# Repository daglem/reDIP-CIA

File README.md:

# reDIP CIA

## MOS 6520 PIA / MOS 6522 VIA / MOS 6526/8520/8521 CIA FPGA replacement

## Overview
The reDIP CIA is an open source FPGA board which combines the following in a
DIP-40 size package:

* Lattice iCE5LP1K FPGA
* 1Mbit FLASH
* 5V tolerant I/O

The reDIP CIA provides an open source hardware platform for MOS 6520 PIA /
MOS 6522 VIA / MOS 6526/8520/8521 CIA replacements.

Designs for the iCE5LP1K FPGA can be processed by
[yosys](https://github.com/YosysHQ/yosys/) and
[nextpnr](https://github.com/YosysHQ/nextpnr/).

## I/O interfaces

### DIP-40 header pins:

* 5V input
* 35 FPGA GPIO
* 3 FPGA open-drain I/O
* GND

All FPGA header I/O is 5V tolerant, and can drive 5V TTL.

### SPI / programming header:

A separate header footprint is provided for (Q)SPI flash programming, with
pinout borrowed from the
[iCEBreaker Bitsy](https://codeberg.org/icebreaker-fpga/icebreaker).

## MOS 6526/8521 and MOS 8520 CIA compatibility

The board is fully pin compatible with the venerable MOS 6526/8521 and MOS 8520
CIA chips.

Cycle accurate emulation of the MOS 6526/8521 and MOS 8520 CIA chips has been
implemented in [gateware](gateware/CIA/), configurable via [software](software/).

## MOS 6522 VIA compatibility

Cycle accurate emulation of the MOS 6522 VIA chip has been implemented in
[gateware](gateware/VIA/).

## MOS 6520 PIA compatibility

Cycle accurate emulation of the MOS 6520 PIA chip has been implemented in
[gateware](gateware/PIA/).

## Thanks

The gateware implementations would not have been possible without the
[outstanding work](https://6502.org/forum/viewtopic.php?t=7427) on varius MOS
chips by Frank "androSID" Wolf and Dieter "ttlworks" Müller.

Wagner Rodriguez has tested the 8520 CIA implementation with the [Versatile
Amiga Testprogram](https://aminet.net/package/util/misc/VATestprogram).

Mateusz Nalewajski has hunted down and fixed two bugs while working on
integrating the VIA gateware in
[icepi-zero-c64](https://github.com/m1nl/icepi-zero-c64).

André Fachat has tested the VIA and PIA implementations with his [PET PIA and
VIA test suite](https://github.com/fachat/pet_viapia_tests).

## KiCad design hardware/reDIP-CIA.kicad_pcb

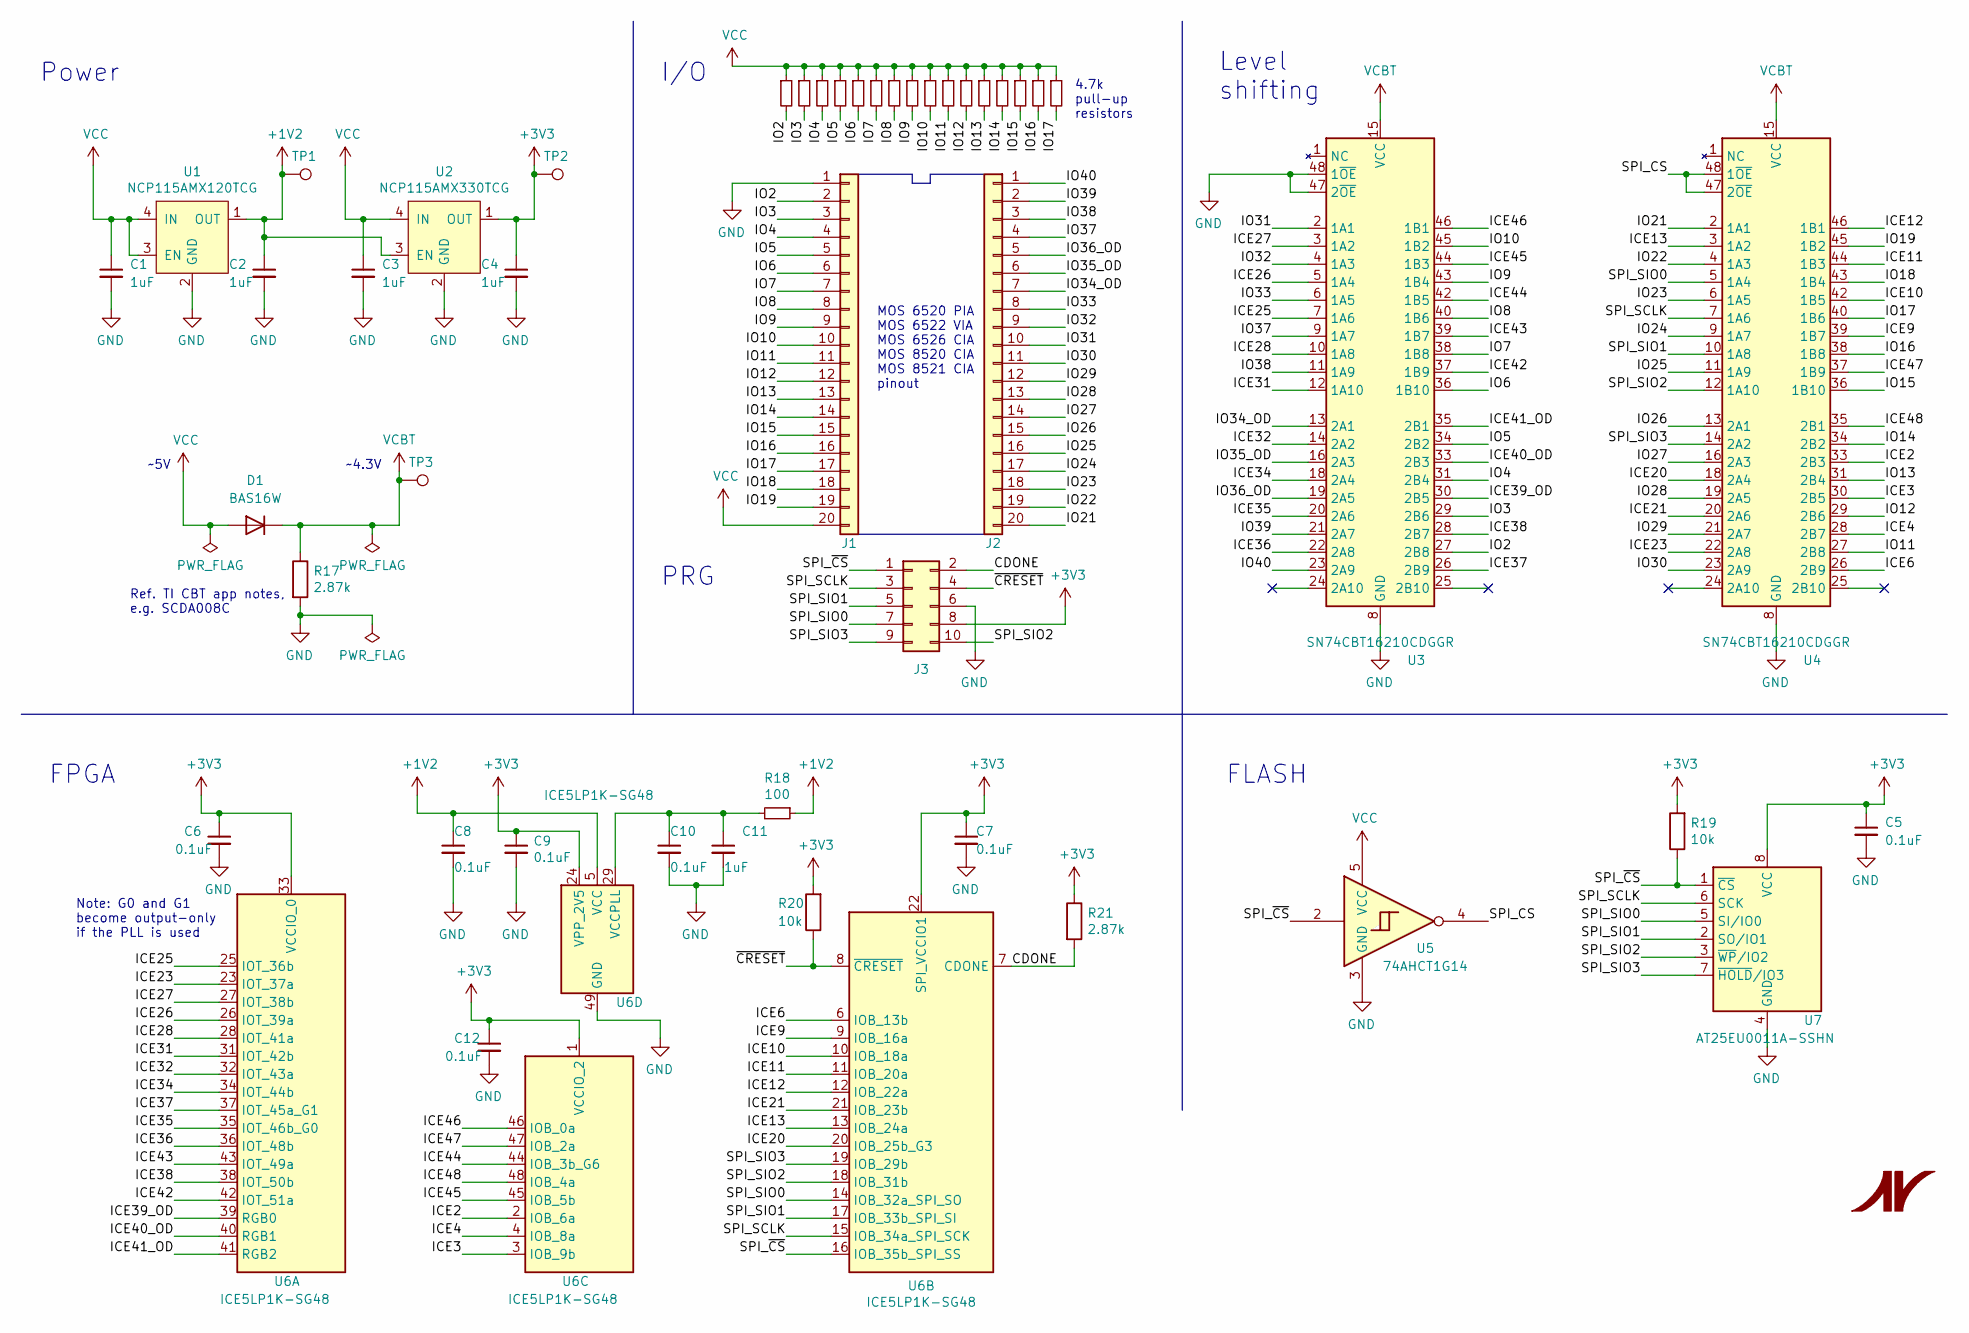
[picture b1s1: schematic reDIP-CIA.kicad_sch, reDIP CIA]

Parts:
C1, C3: 1uF; C_0402_1005Metric
C2, C4, C11: 1uF; C_0201_0603Metric
C5, C6, C7, C8, C9, C10, C12: 0.1uF; C_0201_0603Metric
D1: BAS16W; SOT-323_SC-70
J1, J2: Conn_01x20; PinHeader_1x20_P2.54mm_Vertical_Machined
J3: Conn_02x05_Odd_Even; PinHeader_2x05_P2.54mm_Vertical
R1, R2, R3, R4, R5, R6, R7, R8, R9, R10, R11, R12, R13, R14, R15, R16: 4.7k; R_0201_0603Metric
R17, R21: 2.87k; R_0201_0603Metric
R18: 100; R_0201_0603Metric
R19, R20: 10k; R_0201_0603Metric
TP1, TP2, TP3: TestPoint; TestPoint_Pad_D1.00mm
U1: NCP115AMX120TCG; CASE_711AJ_1.0x1.0mm_P0.65mm
U2: NCP115AMX330TCG; CASE_711AJ_1.0x1.0mm_P0.65mm
U3, U4: SN74CBT16210CDGGR; TSSOP-48_6.1x12.5mm_P0.5mm
U5: 74AHCT1G14; SOT-353_SC-70-5
U6: ICE5LP1K-SG48; QFN-48-1EP_7x7mm_P0.5mm_EP5.6x5.6mm
U7: AT25EU0011A-SSHN; SOIC-8_3.9x4.9mm_P1.27mm

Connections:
+1V2: C2.1, C8.1, R18.1, TP1.1, U1.1 (OUT), U2.3 (EN), U6.5 (VCC), U6.30 (VCC)
+3V3: C4.1, C5.1, C6.1, C7.1, C9.1, C12.1, J3.8, R19.2, R20.2, R21.1, TP2.1, U2.1 (OUT), U6.1 (VCCIO_2), U6.22 (SPI_VCCIO1), U6.24 (VPP_2V5), U6.33 (VCCIO_0), U7.8 (VCC)
/CDONE: J3.2, R21.2, U6.7 (CDONE)
/ICE2: U4.33 (2B3), U6.2 (IOB_6a)
/ICE3: U4.30 (2B5), U6.3 (IOB_9b)
/ICE4: U4.28 (2B7), U6.4 (IOB_8a)
/ICE6: U4.26 (2B9), U6.6 (IOB_13b)
/ICE9: U4.39 (1B7), U6.9 (IOB_16a)
/ICE10: U4.42 (1B5), U6.10 (IOB_18a)
/ICE11: U4.44 (1B3), U6.11 (IOB_20a)
/ICE12: U4.46 (1B1), U6.12 (IOB_22a)
/ICE13: U4.3 (1A2), U6.13 (IOB_24a)
/ICE20: U4.18 (2A4), U6.20 (IOB_25b_G3)
/ICE21: U4.20 (2A6), U6.21 (IOB_23b)
/ICE23: U4.22 (2A8), U6.23 (IOT_37a)
/ICE25: U3.7 (1A6), U6.25 (IOT_36b)
/ICE26: U3.5 (1A4), U6.26 (IOT_39a)
/ICE27: U3.3 (1A2), U6.27 (IOT_38b)
/ICE28: U3.10 (1A8), U6.28 (IOT_41a)
/ICE31: U3.12 (1A10), U6.31 (IOT_42b)
/ICE32: U3.14 (2A2), U6.32 (IOT_43a)
/ICE34: U3.18 (2A4), U6.34 (IOT_44b)
/ICE35: U3.20 (2A6), U6.35 (IOT_46b_G0)
/ICE36: U3.22 (2A8), U6.36 (IOT_48b)
/ICE37: U3.26 (2B9), U6.37 (IOT_45a_G1)
/ICE38: U3.28 (2B7), U6.38 (IOT_50b)
/ICE39_OD: U3.30 (2B5), U6.39 (RGB0)
/ICE40_OD: U3.33 (2B3), U6.40 (RGB1)
/ICE41_OD: U3.35 (2B1), U6.41 (RGB2)
/ICE42: U3.37 (1B9), U6.42 (IOT_51a)
/ICE43: U3.39 (1B7), U6.43 (IOT_49a)
/ICE44: U3.42 (1B5), U6.44 (IOB_3b_G6)
/ICE45: U3.44 (1B3), U6.45 (IOB_5b)
/ICE46: U3.46 (1B1), U6.46 (IOB_0a)
/ICE47: U4.37 (1B9), U6.47 (IOB_2a)
/ICE48: U4.35 (2B1), U6.48 (IOB_4a)
/IO2: J1.2, R1.2, U3.27 (2B8)
/IO3: J1.3, R2.2, U3.29 (2B6)
/IO4: J1.4, R3.2, U3.31 (2B4)
/IO5: J1.5, R4.2, U3.34 (2B2)
/IO6: J1.6, R5.2, U3.36 (1B10)
/IO7: J1.7, R6.2, U3.38 (1B8)
/IO8: J1.8, R7.2, U3.40 (1B6)
/IO9: J1.9, R8.2, U3.43 (1B4)
/IO10: J1.10, R9.2, U3.45 (1B2)
/IO11: J1.11, R10.2, U4.27 (2B8)
/IO12: J1.12, R11.2, U4.29 (2B6)
/IO13: J1.13, R12.2, U4.31 (2B4)
/IO14: J1.14, R13.2, U4.34 (2B2)
/IO15: J1.15, R14.2, U4.36 (1B10)
/IO16: J1.16, R15.2, U4.38 (1B8)
/IO17: J1.17, R16.2, U4.40 (1B6)
/IO18: J1.18, U4.43 (1B4)
/IO19: J1.19, U4.45 (1B2)
/IO21: J2.20, U4.2 (1A1)
/IO22: J2.19, U4.4 (1A3)
/IO23: J2.18, U4.6 (1A5)
/IO24: J2.17, U4.9 (1A7)
/IO25: J2.16, U4.11 (1A9)
/IO26: J2.15, U4.13 (2A1)
/IO27: J2.14, U4.16 (2A3)
/IO28: J2.13, U4.19 (2A5)
/IO29: J2.12, U4.21 (2A7)
/IO30: J2.11, U4.23 (2A9)
/IO31: J2.10, U3.2 (1A1)
/IO32: J2.9, U3.4 (1A3)
/IO33: J2.8, U3.6 (1A5)
/IO34_OD: J2.7, U3.13 (2A1)
/IO35_OD: J2.6, U3.16 (2A3)
/IO36_OD: J2.5, U3.19 (2A5)
/IO37: J2.4, U3.9 (1A7)
/IO38: J2.3, U3.11 (1A9)
/IO39: J2.2, U3.21 (2A7)
/IO40: J2.1, U3.23 (2A9)
/SPI_CS: U4.47 (2~OE), U4.48 (1~OE), U5.4
/SPI_SCLK: J3.3, U4.7 (1A6), U6.15 (IOB_34a_SPI_SCK), U7.6 (SCK)
/SPI_SIO0: J3.7, U4.5 (1A4), U6.14 (IOB_32a_SPI_SO), U7.5 (SI/IO0)
/SPI_SIO1: J3.5, U4.10 (1A8), U6.17 (IOB_33b_SPI_SI), U7.2 (SO/IO1)
/SPI_SIO2: J3.10, U4.12 (1A10), U6.18 (IOB_31b), U7.3 (~WP/IO2)
/SPI_SIO3: J3.9, U4.14 (2A2), U6.19 (IOB_29b), U7.7 (~HOLD/IO3)
/SPI_~CS: J3.1, R19.1, U5.2, U6.16 (IOB_35b_SPI_SS), U7.1 (~CS)
/~CRESET: J3.4, R20.1, U6.8 (~CRESET)
GND: C1.2, C2.2, C3.2, C4.2, C5.2, C6.2, C7.2, C8.2, C9.2, C10.2, C11.2, C12.2, J1.1, J3.6, R17.2, U1.2 (GND), U2.2 (GND), U3.8 (GND), U3.17 (GND), U3.32 (GND), U3.41 (GND), U3.47 (2~OE), U3.48 (1~OE), U4.8 (GND), U4.17 (GND), U4.32 (GND), U4.41 (GND), U5.3 (GND), U6.49 (GND), U7.4 (GND)
unnamed: C10.1, C11.1, R18.2, U6.29 (VCCPLL)
VCBT: D1.3 (K), R17.1, TP3.1, U3.15 (VCC), U4.15 (VCC)
VCC: C1.1, C3.1, D1.1 (A), J1.20, R1.1, R2.1, R3.1, R4.1, R5.1, R6.1, R7.1, R8.1, R9.1, R10.1, R11.1, R12.1, R13.1, R14.1, R15.1, R16.1, U1.3 (EN), U1.4 (IN), U2.4 (IN), U5.5 (VCC)

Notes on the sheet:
MOS 6520 PIA MOS 6522 VIA MOS 6526 CIA MOS 8520 CIA MOS 8521 CIA pinout
PRG
Ref. TI CBT app notes, e.g. SCDA008C
~4.3V
FLASH
FPGA
Power
4.7k pull-up resistors
I/O
Level shifting
~5V
Note: G0 and G1 become output-only if the PLL is used

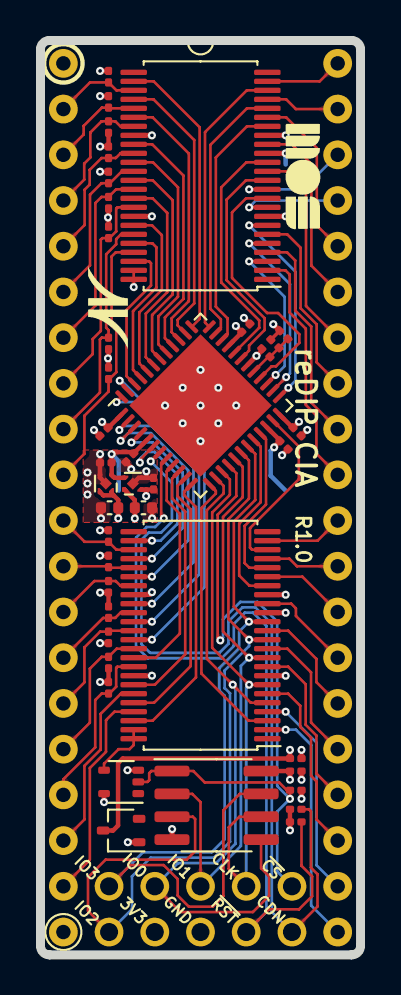
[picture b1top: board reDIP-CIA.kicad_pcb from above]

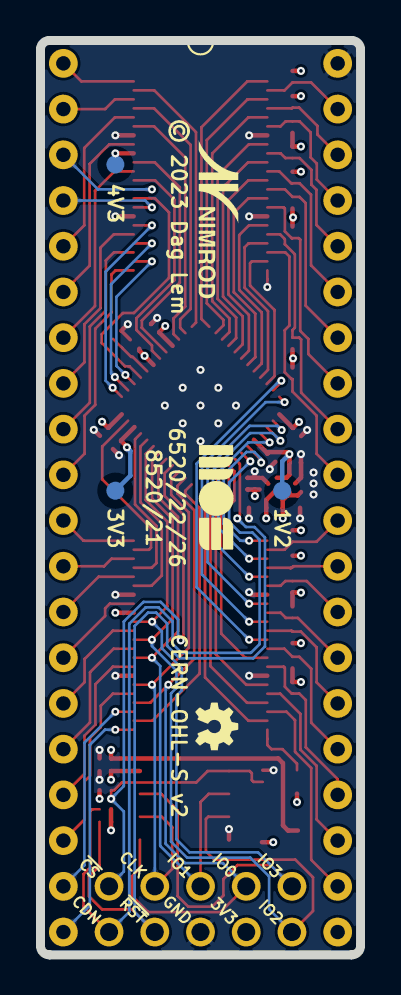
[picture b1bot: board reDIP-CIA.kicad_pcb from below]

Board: 4 copper layers, 17.8 x 50.8 mm, 56 parts (14 on the bottom side), 86 nets.

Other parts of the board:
SolderMask_D0.25mm, SolderMask_D0.25mm#2, SolderMask_D0.25mm#3, SolderMask_D0.25mm#4, SolderMask_D0.25mm#5, SolderMask_D0.25mm#6, SolderMask_D0.25mm#7, SolderMask_D0.25mm#8, SolderMask_D0.25mm#9: SolderMask_D0.25mm

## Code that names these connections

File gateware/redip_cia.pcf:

# MOS 6526 / 8520 / 8521 CIA
# Pin Constraints File for iCE5LP1K-SG48

# CIA pin  1 = VSS
# CIA pin 20 = VCC

# CIA pin 2 - 19
set_io -nowarn PA0  36
set_io -nowarn PA1  35
set_io -nowarn PA2  34
set_io -nowarn PA3  32
set_io -nowarn PA4  31
set_io -nowarn PA5  28
set_io -nowarn PA6  25
set_io -nowarn PA7  26

set_io -nowarn PB0  27
set_io -nowarn PB1  23
set_io -nowarn PB2  21
set_io -nowarn PB3  20
set_io -nowarn PB4  19
set_io -nowarn PB5  18
set_io -nowarn PB6  17
set_io -nowarn PB7  15

set_io -nowarn PC   14
set_io -nowarn TOD  13

# CIA pin 40 - 21
set_io -nowarn CNT  37
set_io -nowarn SP   38
set_io -nowarn RS0  42
set_io -nowarn RS1  43
set_io -nowarn RS2  39
set_io -nowarn RS3  40
set_io -nowarn RES  41

set_io -nowarn D0   44
set_io -nowarn D1   45
set_io -nowarn D2   46
set_io -nowarn D3    6
set_io -nowarn D4    4
set_io -nowarn D5    3
set_io -nowarn D6    2
set_io -nowarn D7   48

set_io -nowarn PHI2 47
set_io -nowarn FLAG  9
set_io -nowarn CS   10
set_io -nowarn R_W  11
set_io -nowarn IRQ  12

# SPI flash pins
set_io -nowarn SPI_CS 16

# Other SPI flash pins are shared as follows:

#   SPI_SIO0 - 14 - PC
#   SPI_SCLK - 15 - PB7
#   SPI_SIO1 - 17 - PB6
#   SPI_SIO2 - 18 - PB5
#   SPI_SIO3 - 19 - PB4

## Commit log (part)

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2023-11-07 Added pin constraints files
2025-01-12 Upgrade to KiCad 8
2025-01-12 Add teardrops back again
    Teardrops were lost in conversion to KiCad 8.
2025-03-16 Manufacture updates
2025-03-16 First stab at gateware
    This is based on the excellent "8521 dissection" by Dieter "ttlworks" Müller
    and Frank Wolf at http://forum.6502.org/viewtopic.php?f=4&t=7418
    The implementation has not been tested yet, so there will be bugs!
2025-03-19 Correct clocking of TOD input divider
2025-03-19 Add flash prog target to Makefile
2025-03-21 Rename chip_t to model_t
2025-03-21 Corrections and enhancements to simulator program
2025-03-23 Corrections to simulator program
2025-04-08 Fix various issues revealed by simulation
    Fixes all over the place, getting closer to correct MOS 8521 emulation.
    The serial port and MOS 6526 interrupts still need some work.
2025-06-26 Fix more issues revealed by simulation
    Getting fairly close to correct MOS 8521 emulation, however
    there are still issues with the serial port.
2025-11-09 Tweak output order of interrupts in simulation
2025-11-26 Improve error handling in simulation
2025-11-26 Clean up reset handling
    Remove support for one-cycle resets in simulation.
2025-11-26 Clean up code for serial port
    Still not passing VICE cia-sdr-icr tests.
2025-11-27 Clean up synchronized edge detection
2025-11-27 Emulate open drain SP and CNT pads in simulation
    This is a step towards passing the VICE cia-sdr-icr tests.
2026-01-14 All serial port tests are now passing in simulation
    This took a lot of effort! The VICE cia-sdr-icr tests don't actually
    test the contents of the ICR register after switching SP MODE from
    OUTPUT to INPUT, and consequently emulators don't get this right.
    A new test will be added to https://sourceforge.net/p/vice-emu/bugs/1219/
2026-01-17 All TOD tests are now passing in simulation
    It is not possible to map out all cycle accurate behavior of the TOD in
    an unmodified C64, since the TOD input is fed from an external signal.
    Hence, emulators do not currently sport cycle accurate TOD behavior.
    The following flags can be provided to the simulation in order to match
    the behavior of emulators:
    * TOD_PHI20_NODELAY: Use PHI2 instead of PHI2/4 for internal clocking
2026-01-22 Add information on the gateware implementation
2026-01-27 Correct timer outputs on port B
2026-01-29 Correct timer toggle outputs on port B
2026-02-25 The MOS 8521 gateware now passes all tests
    A lot of effort again! A couple of strange things are going on in the
    interrupt block. Referring to the 8521 schematic at
    http://forum.6502.org/viewtopic.php?f=4&t=7418 - a missing metal contact
    to VCC makes an inverter in the path to IFR_CLR always output 0, and
    extremely long polysilicon gate strips cause delays in driving the ICR
    register output bits to 0. That's my theory, at least :-)
2026-03-07 The MOS 6526 gateware now passes all tests
    The final pieces finally fell into place when I managed to make sense of
    the ICR block in the die shot at
    http://siliconpr0n.org/archive/doku.php?id=mcmaster:mos:6526
2026-03-17 Add cells_sim
2026-03-29 Real-time configuration WIP
2026-05-16 Split CRA and CRB out into separate module instances
2026-05-18 MOS 8520 emulation
    Completely untested!
2026-05-25 Runtime configuration of CIA model
2026-05-25 C64 configuration program
2026-05-25 Simplified calculation of TOD HR
2026-05-25 Fix link to software
2026-05-26 Add make option NO_MOS8520=
2026-06-18 MOS 6522 emulation
    Completely untested!
2026-06-20 MOS 6520 emulation
    Completely untested!
2026-06-26 VIA: Fix register R/W. Set IFR[7]
2026-06-26 VIA: Simulation

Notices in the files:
hardware/reDIP-CIA.kicad_pcb:
© 2023 Dag Lem
Licensed under CERN-OHL-S v2 (https://ohwr.org/cern_ohl_s_v2.txt)
CERN-OHL-S v2
